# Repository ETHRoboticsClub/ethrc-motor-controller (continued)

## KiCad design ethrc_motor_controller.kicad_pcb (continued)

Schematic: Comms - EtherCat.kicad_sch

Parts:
C115, C118, C120, C122, C123, C124, C125, C126, C127, C128, C129, C130, C131, C132, C133, C134, C135: 100n; C_0402_1005_DensityHigh; Manufacturer Part Number CL05B104KO5NNNC
C116, C117: 10p C0G; C_0402_1005_DensityHigh; Manufacturer Part Number CL05C100JB5NNNC
C119, C121, C161: 1u; C_0603_1608_DensityHigh; Manufacturer Part Number CL10B105KA8NNNC
C136, C137, C138, C139, C140, C141, C142, C143: 10p; C_0402_1005_DensityHigh; Manufacturer Part Number CL05C100JB5NNNC; not fitted
C144, C145: 0.022u; C_0402_1005_DensityHigh; Manufacturer Part Number GCM155R71H223KA55D
C155, C156: 1n X7R 2kV; C_1808_4520Metric; Manufacturer Part Number C1808C102KGRACTU
D18: Red; LED_0603_1608Metric; Manufacturer Part Number LTST-C191KRKT
D19, D24, D25: Green; LED_0603_1608Metric; Manufacturer Part Number LTST-C191KGKT
FB5: 600R@100MHz; L_0603_1608Metric; Manufacturer Part Number BLM18KG601SN1D
J9, J10: SM05B-GHS-TB; JST_GH_SM05B-GHS-TB_1x05-1MP_P1.25mm_Horizontal; Manufacturer Part Number SM05B-GHS-TB
R46, R48, R49, R51, R57, R58, R90, R91: 10k; R_0603_1608_DensityHigh; Manufacturer Part Number CRCW060310K0FKEA
R47, R50, R52, R53: 2.2k; R_0603_1608_DensityHigh; Manufacturer Part Number ERJ-3EKF2201V
R54: 1k; R_0603_1608_DensityHigh; Manufacturer Part Number ERJ-3EKF1001V
R55: 12.1k 1%; R_0603_1608_DensityHigh; Manufacturer Part Number ERJ-3EKF1212V
R56: 22R; R_0402_1005_DensityHigh; Manufacturer Part Number ERJ-2RKF22R0X
R59, R60, R61, R62, R63, R64, R65, R66: 49.9 1%; R_0402_1005_DensityHigh; Manufacturer Part Number ERJ-2RKF49R9X
R67, R68: 330; R_0603_1608_DensityHigh; Manufacturer Part Number ERJ-3EKF3300V
R83, R84: 0R; R_0603_1608_DensityHigh; Manufacturer Part Number CRCW06030000Z0EAHP
R85, R86, R87, R88: 75 1%; R_0603_1608_DensityHigh; Manufacturer Part Number ERJ-3EKF75R0V
T1, T2: H1102NL; Transformer_Pulse_H1100NL; Manufacturer Part Number H1102NL
TP76: ESC_XO_XTAL; TestPoint_Keystone_5000-5004_Miniature; Manufacturer Part Number 5004
TP77: GND; TestPoint_Keystone_5000-5004_Miniature; Manufacturer Part Number 5001
TP78: +3V3_PHY; TestPoint_Pad_D0.5mm
TP79: +1V2_ESC; TestPoint_Pad_D0.5mm
TP80: ESC_OSCVDD12; TestPoint_Pad_D0.5mm
TP81: EE_SCL; TestPoint_Pad_D0.5mm
TP82: EE_SDA; TestPoint_Pad_D0.5mm
TP83: ECAT_P0_TX+; TestPoint_Pad_D0.4mm
TP84: ECAT_P0_TX-; TestPoint_Pad_D0.4mm
TP85: ECAT_P0_RX+; TestPoint_Pad_D0.4mm
TP86: ECAT_P0_RX-; TestPoint_Pad_D0.4mm
TP87: ECAT_P1_TX+; TestPoint_Pad_D0.4mm
TP88: ECAT_P1_TX-; TestPoint_Pad_D0.4mm
TP89: ECAT_P1_RX+; TestPoint_Pad_D0.4mm
TP90: ECAT_P1_RX-; TestPoint_Pad_D0.4mm
U8: 24LC32AT-I/OT; SOT-23-5; Manufacturer Part Number 24LC32AT-I/OT
U9: LAN9253-V/R4X; QFN64_R4X_MCH; Manufacturer Part Number LAN9253-V/R4X
Y1: 25MHz 8pF; ABM8G_ABR; Manufacturer Part Number ABM8G-25.000MHZ-4Y-T3

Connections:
+1V2_ESC: C122.1, C124.1, C126.1, C128.1, C130.1, C161.1, TP79.1, U9.6 (VDDCR), U9.24 (VDDCR), U9.38 (VDDCR), U9.56 (VDD12TX1), U9.59 (VDD12TX2)
+3V3: C115.2, C121.1, C123.1, C125.1, C127.1, C129.1, C131.1, C132.1, D19.2 (A), FB5.2, R49.2, R50.1, R51.1, R52.1, R90.1, R91.1, U8.4 (VCC), U9.5 (VDD33), U9.7 (REG_EN), U9.14 (VDDIO), U9.20 (VDDIO), U9.32 (VDDIO), U9.37 (VDDIO), U9.47 (VDDIO); also elsewhere on the board
+3V3_PHY: C133.1, C134.1, C135.1, C144.1, C145.1, FB5.1, R59.1, R60.1, R61.1, R62.1, R63.1, R64.1, R65.1, R66.1, T1.2 (TCT), T1.7 (RCT), T2.2 (TCT), T2.7 (RCT), TP78.1, U9.51 (VDD33TXRX1), U9.58 (VDD33BIAS), U9.64 (VDD33TXRX2)
/Project Architecture/Comms - EtherCat/ECAT_P0_CBL_RX+: J9.3, T1.11 (RX+)
/Project Architecture/Comms - EtherCat/ECAT_P0_CBL_RX-: J9.2, T1.9 (RX-)
/Project Architecture/Comms - EtherCat/ECAT_P0_CBL_TX+: J9.5, T1.16 (TX+)
/Project Architecture/Comms - EtherCat/ECAT_P0_CBL_TX-: J9.4, T1.14 (TX-)
/Project Architecture/Comms - EtherCat/ECAT_P0_RX+: C140.1, R63.2, T1.1 (TD+), TP85.1, U9.55 (RXPA)
/Project Architecture/Comms - EtherCat/ECAT_P0_RX-: C142.1, R65.2, T1.3 (TD-), TP86.1, U9.54 (RXNA)
/Project Architecture/Comms - EtherCat/ECAT_P0_TX+: C136.1, R59.2, T1.6 (RD+), TP83.1, U9.53 (TXPA)
/Project Architecture/Comms - EtherCat/ECAT_P0_TX-: C138.1, R61.2, T1.8 (RD-), TP84.1, U9.52 (TXNA)
/Project Architecture/Comms - EtherCat/ECAT_P1_CBL_RX+: J10.3, T2.11 (RX+)
/Project Architecture/Comms - EtherCat/ECAT_P1_CBL_RX-: J10.2, T2.9 (RX-)
/Project Architecture/Comms - EtherCat/ECAT_P1_CBL_TX+: J10.5, T2.16 (TX+)
/Project Architecture/Comms - EtherCat/ECAT_P1_CBL_TX-: J10.4, T2.14 (TX-)
/Project Architecture/Comms - EtherCat/ECAT_P1_RX+: C141.1, R64.2, T2.8 (RD-), TP89.1, U9.60 (RXPB)
/Project Architecture/Comms - EtherCat/ECAT_P1_RX-: C143.1, R66.2, T2.6 (RD+), TP90.1, U9.61 (RXNB)
/Project Architecture/Comms - EtherCat/ECAT_P1_TX+: C137.1, R60.2, T2.3 (TD-), TP87.1, U9.62 (TXPB)
/Project Architecture/Comms - EtherCat/ECAT_P1_TX-: C139.1, R62.2, T2.1 (TD+), TP88.1, U9.63 (TXNB)
/Project Architecture/Comms - EtherCat/EE_SCL: R50.2, TP81.1, U8.1 (SCL), U9.43 (EESCL/EE_EMUL2)
/Project Architecture/Comms - EtherCat/EE_SDA: R52.2, TP82.1, U8.3 (SDA), U9.42 (EESDA/EE_EMUL1)
/Project Architecture/Comms - EtherCat/ESC_CLK25: R54.1, U9.8 (CLK_25/XTAL_MODE)
/Project Architecture/Comms - EtherCat/ESC_CS: R90.2, U9.50 (SCS#); also elsewhere on the board
/Project Architecture/Comms - EtherCat/ESC_ERR: R47.1, R48.1, U9.9 (ERRLED/100FD_B)
/Project Architecture/Comms - EtherCat/ESC_IRQ: R91.2, U9.44 (IRQ); also elsewhere on the board
/Project Architecture/Comms - EtherCat/ESC_LINK0: R58.1, R67.1, U9.48 (LINKACTLED0/CHIP_MODE0)
/Project Architecture/Comms - EtherCat/ESC_LINK1: R57.1, R68.1, U9.46 (LINKACTLED1/CHIP_MODE1)
/Project Architecture/Comms - EtherCat/ESC_MISO: R56.2; also elsewhere on the board
/Project Architecture/Comms - EtherCat/ESC_MISO_ESC: R56.1, U9.13 (SO/SIO1)
/Project Architecture/Comms - EtherCat/ESC_MOSI: U9.17 (SI/SIO0); also elsewhere on the board
/Project Architecture/Comms - EtherCat/ESC_OSCVDD12: C119.1, C120.1, TP80.1, U9.3 (OSCVDD12)
/Project Architecture/Comms - EtherCat/ESC_RBIAS: R55.1, U9.57 (RBIAS)
/Project Architecture/Comms - EtherCat/ESC_RST: C118.1, R51.2, U9.11 (RST#); also elsewhere on the board
/Project Architecture/Comms - EtherCat/ESC_RUN: R49.1, R53.2, U9.45 (RUNLED/E2PSIZE)
/Project Architecture/Comms - EtherCat/ESC_SCLK: U9.19 (SCK); also elsewhere on the board
/Project Architecture/Comms - EtherCat/ESC_SYNC0: U9.34 (SYNC0/LATCH0); also elsewhere on the board
/Project Architecture/Comms - EtherCat/ESC_SYNC1: U9.18 (SYNC1/LATCH1); also elsewhere on the board
/Project Architecture/Comms - EtherCat/ESC_XI: R84.1, U9.1 (OSCI)
/Project Architecture/Comms - EtherCat/ESC_XO: R83.2, U9.2 (OSCO)
/Project Architecture/Comms - EtherCat/ESC_XO_XTAL: C116.1, R83.1, TP76.1, Y1.1
CHASSIS: C155.2, C156.2, J9.1, J9.MP1, J9.MP2, J10.1, J10.MP1, J10.MP2; also elsewhere on the board
GND: C115.1, C116.2, C117.2, C118.2, C119.2, C120.2, C121.2, C122.2, C123.2, C124.2, C125.2, C126.2, C127.2, C128.2, C129.2, C130.2, C131.2, C132.2, C133.2, C134.2, C135.2, C136.2, C137.2, C138.2, C139.2, C140.2, C141.2, C142.2, C143.2, C144.2, C145.2, C161.2, D18.1 (K), D24.1 (K), D25.1 (K), R46.1, R48.2, R54.2, R55.2, R57.2, R58.2, TP77.1, U8.2 (VSS), U9.4 (OSCVSS), U9.41 (TESTMODE), U9.65 (VSS(EP)), Y1.2, Y1.4; also elsewhere on the board
unnamed: C117.1, R84.2, Y1.3
unnamed: C155.1, R85.2, R86.2
unnamed: C156.1, R87.2, R88.2
unnamed: D18.2 (A), R47.2
unnamed: D19.1 (K), R53.1
unnamed: D24.2 (A), R67.2
unnamed: D25.2 (A), R68.2
unnamed: R86.1, T1.10 (RXCT)
unnamed: R85.1, T1.15 (TXCT)
unnamed: R88.1, T2.10 (RXCT)
unnamed: R87.1, T2.15 (TXCT)
unnamed: R46.2, U8.5 (WP)

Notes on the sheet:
strap CHIP_MODE0
25 MHz crystal
+3V3_PHY: pins 51, 58, 64, T1/T2 centre taps, FB5 output
22R at U9
SII EEPROM (I2C address 0x50)
tie low
strap 100FD_B
Mode strap, reset, SPI MISO series
crystal mode
+1V2_ESC (internal regulator): C161 1u low-ESR (DS00003421B 4.1.1) at VDDCR pin 6; 24, 38, 56, 59 100n each
ETHERCAT - LAN9253 (SPI PDI, 2 PORTS), Magnetics, SII EEPROM
49.9R terminations to +3V3_PHY (at the LAN9253 pins)
EtherCAT indicators + strap resistors (straps read at reset)
unused in SPI mode
H1102NL magnetics, Bob Smith (75R + 1n 2kV), JST-GH connectors
+3V3: VDD33 (5) 1u+100n, VDDIO (14, 20, 32, 37, 47) 100n each, U3 100n
strap CHIP_MODE1
strap E2PSIZE=1
EtherCAT test points (TP76/TP77 hooks on the BOM, the others are bare pads)
LAYOUT NOTE: ETHERCAT * TX/RX pairs 100 ohm differential, matched in-pair, short; 49.9R at the U9 pins. * Keep PHY side and cable side of T1/T2 apart; no GND plane under the cable side and the GH connectors except the Bob Smith cap return; C155/C156 right at the centre taps, returned to CHASSIS. * 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
DESIGN NOTE: WP low: master can write the SII
[${#}] ${TITLE}
DESIGN NOTE: T1/T2 chip side deliberately swapped (2026-11-22) so every pair routes on L1 without vias: port 0: U9 TX pair -> T1 RD pins 6/8, RX pair -> TD pins 1/3 (Auto-MDIX sorts TX/RX); port 1: P and N exchanged in both pairs at T2 (automatic polarity correction). Microchip LAN9253 HW design ch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

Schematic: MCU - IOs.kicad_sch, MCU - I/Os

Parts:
C12, C13: 100n X7R 50V; C_0402_1005_DensityHigh; Manufacturer Part Number GCM155R71H104KE02J
C14, C15, C16: 1n; C_0402_1005_DensityHigh; Manufacturer Part Number AC0402KRX7R8BB102
D1: PESD4USB3U-TBSX; SOT1176D; Manufacturer Part Number PESD4USB3U-TBSX
J15: Conn_ARM_SWD_TagConnect_TC2030-NL; Tag-Connect_TC2030-IDC-NL_2x03_P1.27mm_Vertical
R1, R2, R3, R4, R5, R6, R7: 22R 1%; R_0402_1005_DensityHigh; Manufacturer Part Number ERJ-2RKF22R0X
R8, R9: 22; R_0402_1005_DensityHigh; Manufacturer Part Number RC0402FR-0722RL
R77: 10k; R_0402_1005_DensityHigh; Manufacturer Part Number CRCW040210K0FKED
TP1: MOTOR_ENABLE; TestPoint_Pad_D0.5mm
TP2: MOTOR_HIZ; TestPoint_Pad_D0.5mm
TP3: MOTOR_FAULT; TestPoint_Pad_D0.5mm
TP4: DRV_SCLK; TestPoint_Pad_D0.5mm
TP5: DRV_MISO; TestPoint_Pad_D0.5mm
TP6: DRV_MOSI; TestPoint_Pad_D0.5mm
TP7: DRV_CS; TestPoint_Pad_D0.5mm
TP8: PWM_PHASEA; TestPoint_Pad_D0.5mm
TP9: PWM_PHASEB; TestPoint_Pad_D0.5mm
TP10: PWM_PHASEC; TestPoint_Pad_D0.5mm
TP11: SOA; TestPoint_Pad_D0.5mm
TP12: SOB; TestPoint_Pad_D0.5mm
TP13: SOC; TestPoint_Pad_D0.5mm
TP14: SWDIO; TestPoint_Pad_D0.5mm
TP15: SWCLK; TestPoint_Pad_D0.5mm
TP16: NRST; TestPoint_Pad_D0.5mm
TP17: ESC_RST; TestPoint_Pad_D0.5mm
TP18: ESC_SCLK; TestPoint_Pad_D0.5mm
TP19: ESC_MISO; TestPoint_Pad_D0.5mm
TP20: ESC_MOSI; TestPoint_Pad_D0.5mm
TP21: ESC_CS; TestPoint_Pad_D0.5mm
TP22: ESC_IRQ; TestPoint_Pad_D0.5mm
TP23: ESC_SYNC0; TestPoint_Pad_D0.5mm
TP24: ENC_SCLK; TestPoint_Pad_D0.5mm
TP25: ENC_MISO; TestPoint_Pad_D0.5mm
TP26: ENC_MOSI; TestPoint_Pad_D0.5mm
TP27: ENC_BRD_CS; TestPoint_Pad_D0.5mm
TP28: ENC_EXT_CS; TestPoint_Pad_D0.5mm
TP31: LED_DBG; TestPoint_Pad_D0.5mm
TP32: LED_PWR; TestPoint_Pad_D0.5mm
TP33: FD_CAN_RX; TestPoint_Pad_D0.5mm
TP34: FDCAN_TX; TestPoint_Pad_D0.5mm
TP35: FAN_CTRL; TestPoint_Pad_D0.5mm
TP36: SENSE_TEMP_MOT; TestPoint_Pad_D0.5mm
TP37: SENSE_TEMP_FET; TestPoint_Pad_D0.5mm
TP38: SENSE_VBAT; TestPoint_Pad_D0.5mm
TP75: ESC_SYNC1; TestPoint_Pad_D0.5mm
U1: STM32G474RET3; LQFP-64_10x10mm_P0.5mm; Manufacturer Part Number STM32G474RET3

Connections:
+3V3: C12.1, J15.5 (GND); also elsewhere on the board
/Project Architecture/Comms - EtherCat/ESC_CS: TP21.1, U1.33 (PB11); also elsewhere on the board
/Project Architecture/Comms - EtherCat/ESC_IRQ: TP22.1, U1.41 (PC9); also elsewhere on the board
/Project Architecture/Comms - EtherCat/ESC_MISO: TP19.1, U1.36 (PB14); also elsewhere on the board
/Project Architecture/Comms - EtherCat/ESC_MOSI: R3.2, TP20.1; also elsewhere on the board
/Project Architecture/Comms - EtherCat/ESC_RST: TP17.1, U1.44 (PA10); also elsewhere on the board
/Project Architecture/Comms - EtherCat/ESC_SCLK: R4.2, TP18.1; also elsewhere on the board
/Project Architecture/Comms - EtherCat/ESC_SYNC0: TP23.1, U1.39 (PC7); also elsewhere on the board
/Project Architecture/Comms - EtherCat/ESC_SYNC1: TP75.1, U1.40 (PC8); also elsewhere on the board
/Project Architecture/Comms - FD-CAN/FDCAN_RX: TP33.1, U1.58 (PB5); also elsewhere on the board
/Project Architecture/Comms - FD-CAN/FDCAN_TX: TP34.1, U1.59 (PB6); also elsewhere on the board
/Project Architecture/MCU - IOs/BOARD_VERSION: U1.18 (PA4); also elsewhere on the board
/Project Architecture/MCU - IOs/BOOT0: R77.1, U1.61 (PB8)
/Project Architecture/MCU - IOs/DRV_CS: TP7.1, U1.56 (PB3); also elsewhere on the board
/Project Architecture/MCU - IOs/DRV_MISO: TP5.1, U1.53 (PC11); also elsewhere on the board
/Project Architecture/MCU - IOs/DRV_MOSI: R2.1, TP6.1; also elsewhere on the board
/Project Architecture/MCU - IOs/DRV_MOSI_MCU: R2.2, U1.54 (PC12)
/Project Architecture/MCU - IOs/DRV_SCLK: R1.1, TP4.1; also elsewhere on the board
/Project Architecture/MCU - IOs/DRV_SCLK_MCU: R1.2, U1.52 (PC10)
/Project Architecture/MCU - IOs/ENC_BRD_CS: TP27.1, U1.26 (PB2); also elsewhere on the board
/Project Architecture/MCU - IOs/ENC_EXT_CS: TP28.1, U1.51 (PA15); also elsewhere on the board
/Project Architecture/MCU - IOs/ENC_MISO: TP25.1, U1.57 (PB4); also elsewhere on the board
/Project Architecture/MCU - IOs/ENC_MOSI: R9.2, TP26.1; also elsewhere on the board
/Project Architecture/MCU - IOs/ENC_MOSI_MCU: R9.1, U1.21 (PA7)
/Project Architecture/MCU - IOs/ENC_SCLK: R8.2, TP24.1; also elsewhere on the board
/Project Architecture/MCU - IOs/ENC_SCLK_MCU: R8.1, U1.19 (PA5)
/Project Architecture/MCU - IOs/ESC_MOSI_MCU: R3.1, U1.37 (PB15)
/Project Architecture/MCU - IOs/ESC_SCLK_MCU: R4.1, U1.35 (PB13)
/Project Architecture/MCU - IOs/FAN_CTRL: TP35.1, U1.55 (PD2)
/Project Architecture/MCU - IOs/FILTER_SOA: C14.1, R5.1, U1.17 (PA3)
/Project Architecture/MCU - IOs/FILTER_SOB: C15.1, R6.1, U1.20 (PA6)
/Project Architecture/MCU - IOs/FILTER_SOC: C16.1, R7.1, U1.25 (PB1)
/Project Architecture/MCU - IOs/LED_DBG: TP31.1, U1.30 (PB10); also elsewhere on the board
/Project Architecture/MCU - IOs/LED_FAULT: TP32.1, U1.38 (PC6); also elsewhere on the board
/Project Architecture/MCU - IOs/MOTOR_ENABLE: TP1.1, U1.3 (PC14); also elsewhere on the board
/Project Architecture/MCU - IOs/MOTOR_FAULT: TP3.1, U1.8 (PC0); also elsewhere on the board
/Project Architecture/MCU - IOs/MOTOR_HIZ: TP2.1, U1.4 (PC15); also elsewhere on the board
/Project Architecture/MCU - IOs/NRST: C13.1, D1.1 (K), D1.10 (K), J15.3 (~RESET), TP16.1, U1.7 (PG10)
/Project Architecture/MCU - IOs/PWM_PHASEA: TP8.1, U1.14 (PA2); also elsewhere on the board
/Project Architecture/MCU - IOs/PWM_PHASEB: TP9.1, U1.13 (PA1); also elsewhere on the board
/Project Architecture/MCU - IOs/PWM_PHASEC: TP10.1, U1.12 (PA0); also elsewhere on the board
/Project Architecture/MCU - IOs/SENSE_TEMP_FET: TP37.1, U1.34 (PB12); also elsewhere on the board
/Project Architecture/MCU - IOs/SENSE_TEMP_MOT: TP36.1, U1.42 (PA8); also elsewhere on the board
/Project Architecture/MCU - IOs/SENSE_VBAT: TP38.1, U1.43 (PA9); also elsewhere on the board
/Project Architecture/MCU - IOs/SOA: R5.2, TP11.1; also elsewhere on the board
/Project Architecture/MCU - IOs/SOB: R6.2, TP12.1; also elsewhere on the board
/Project Architecture/MCU - IOs/SOC: R7.2, TP13.1; also elsewhere on the board
/Project Architecture/MCU - IOs/SWCLK: D1.4 (K), D1.7 (K), J15.4 (SWCLK), TP15.1, U1.50 (PA14)
/Project Architecture/MCU - IOs/SWDIO: D1.5 (K), D1.6 (K), J15.2 (SWDIO), TP14.1, U1.49 (PA13)
GND: C12.2, C13.2, C14.2, C15.2, C16.2, D1.3 (A), D1.8 (A), J15.1 (VCC), R77.2; also elsewhere on the board

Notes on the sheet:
Flexible I/O worked examples
open-drain output
References:
Flexible I/O source configuration
DESIGN NOTE: Ideally TVS should be connected to chassis but makes it harder to route.
EtherCAT Slave Controller
FD-CAN
LEDs
SWD (Debug) Port
Gate Driver
Fan
Sense
Position Sense
LAYOUT NOTE: Shunt amplifier output low-pass filters. Place near MCU ADC pins.
Board Version Selection
[${#}] ${TITLE}
User LEDs
5Mbps FD-CAN Bus
DESIGN NOTE: Do not forget to flash option bytes when flashing for the first time.
Low-Side Fan Control
Debug
LAYOUT NOTE: Footprint deviates from datasheet and IPC7351 to allow for soldermask sliver between pads according to PCBWay design rules.
Microcontroller I/O Domain
Temperature Sense
Battery Voltage Sense
Test Points
DESIGN NOTE: We use the LQFP64 version to have extra pins for controlling an external fan.
DESIGN NOTE: Only connect GND if connected device does not share ground!
Connections to Gate Driver
Connection to EtherCat Subdevice Controller

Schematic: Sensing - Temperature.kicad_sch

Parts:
C110, C111: 100n X7R 50V; C_0402_1005_DensityHigh; Manufacturer Part Number GCM155R71H104KE02J
D15, D16: BAT41KFILM; D_SOD-523; Manufacturer Part Number BAT41KFILM
J7: S2B-PH-SM4-TB; JST_B2B-PH-SM4-TB; Manufacturer Part Number S2B-PH-SM4-TB
R41, R42: 10k 1%; R_0402_1005_DensityHigh; Manufacturer Part Number RT0402FRE0710KL
TH1: 47k 1% NTC; R_0402_1005_DensityHigh; Manufacturer Part Number NCP15WB473F03RC

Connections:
+A3V3: D15.1 (K), D16.1 (K), R41.1, R42.1; also elsewhere on the board
/Project Architecture/MCU - IOs/SENSE_TEMP_FET: C110.1, D15.2 (A), R41.2, TH1.1; also elsewhere on the board
/Project Architecture/MCU - IOs/SENSE_TEMP_MOT: C111.1, D16.2 (A), J7.1, R42.2; also elsewhere on the board
CHASSIS: J7.MP1, J7.MP2; also elsewhere on the board
GND: C110.2, C111.2, J7.2, TH1.2; also elsewhere on the board

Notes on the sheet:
LAYOUT NOTE: NTCs must be placed close and thermally coupled to relevant heat source. Route away from noisy traces.
MOSFETs Temperature Sensing
Motor Temperature Sensing
[${#}] ${TITLE}
DESIGN NOTE: Ideally connect thermistor with nominal B-Constant 4050-4099K
DESIGN NOTE: Diodes protect against over-voltage.
DESIGN NOTE: Nominal B-Constant 4050-4099K
DESIGN NOTE: Resistor chosen for a 10k 3950K motor thermistor. See make_thermistor_table.py in the firmware repository for more details.

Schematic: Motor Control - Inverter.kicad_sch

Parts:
C98, C99, C102, C103, C106, C107: 3n3 X7R 100V; C_0402_1005_DensityHigh; Manufacturer Part Number GRM155R72A332KA01D; not fitted
C100, C104, C108: 100n X7R 100V; C_1206_3216_DensityHighest; Manufacturer Part Number C1206C104K1RACAUTO
C101, C105, C109: 4u7 X7R 100V; C_1206_3216_DensityHighest; Manufacturer Part Number GRJ31CZ72A475KE01L
D4, D5, D6, D7, D8, D9, D10, D11, D12: BAT41KFILM; D_SOD-523; Manufacturer Part Number BAT41KFILM
J4: Phase A; Pad_Square_Vias_6.5x6.5mm
J5: Phase B; Pad_Square_Vias_6.5x6.5mm
J6: Phase C; Pad_Square_Vias_6.5x6.5mm
NT3: SHNTA_P; NetTie-2_SMD_Pad0.2mm
NT4: SRC_HS_A; NetTie-2_SMD_Pad0.4mm
NT5: SHNTA_N; NetTie-2_SMD_Pad0.2mm
NT6: SHNTB_P; NetTie-2_SMD_Pad0.2mm
NT7: SHNTB_N; NetTie-2_SMD_Pad0.2mm
NT8: SRC_HS_B; NetTie-2_SMD_Pad0.3mm
NT9: SHNTC_P; NetTie-2_SMD_Pad0.2mm
NT10: SHNTC_N; NetTie-2_SMD_Pad0.2mm
NT11: SRC_HS_C; NetTie-2_SMD_Pad0.4mm
Q1, Q2, Q3, Q4, Q5, Q11: FDMT80080DC; FDMT80040DC; Manufacturer Part Number FDMT80080DC; Mouser Part Number 512-FDMT80080DC
R18, R19, R23, R24, R28, R29: 7R5 1% 1/2W; R_0805_2012_DensityHigh; Manufacturer Part Number CRCW08057R50FKEAHP
R20, R25, R30: 0m5 1% 2W; HCS1206FTL500; Manufacturer Part Number HCS1206FTL500
R21, R22, R26, R27, R31, R32: 5R 1% 0.4W; R_0805_2012_DensityHigh; Manufacturer Part Number CSRT0603FT5R00; not fitted

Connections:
+VBAT: C100.1, C101.1, C104.1, C105.1, C108.1, C109.1, Q2.5, Q2.6, Q2.7, Q2.8, Q4.5, Q4.6, Q4.7, Q4.8, Q11.5, Q11.6, Q11.7, Q11.8, R21.2, R26.2, R31.2; also elsewhere on the board
/Project Architecture/Motor Control - Top Level/GHA: D4.1 (K), R18.2; also elsewhere on the board
/Project Architecture/Motor Control - Top Level/GHB: D9.1 (K), R24.1; also elsewhere on the board
/Project Architecture/Motor Control - Top Level/GHC: D11.1 (K), R29.1; also elsewhere on the board
/Project Architecture/Motor Control - Top Level/GLA: D5.1 (K), R19.1; also elsewhere on the board
/Project Architecture/Motor Control - Top Level/GLB: D7.1 (K), R23.1; also elsewhere on the board
/Project Architecture/Motor Control - Top Level/GLC: D10.1 (K), R28.1; also elsewhere on the board
/Project Architecture/Motor Control - Top Level/Motor Control - Inverter/FET_GHA: D4.2 (A), Q11.1, R18.1
/Project Architecture/Motor Control - Top Level/Motor Control - Inverter/FET_GHB: D9.2 (A), Q2.1, R24.2
/Project Architecture/Motor Control - Top Level/Motor Control - Inverter/FET_GHC: D11.2 (A), Q4.1, R29.2
/Project Architecture/Motor Control - Top Level/Motor Control - Inverter/FET_GLA: D5.2 (A), D6.1 (K), Q1.1, R19.2
/Project Architecture/Motor Control - Top Level/Motor Control - Inverter/FET_GLB: D7.2 (A), D8.1 (K), Q3.1, R23.2
/Project Architecture/Motor Control - Top Level/Motor Control - Inverter/FET_GLC: D10.2 (A), D12.1 (K), Q5.1, R28.2
/Project Architecture/Motor Control - Top Level/Motor Control - Inverter/PHA: C98.1, C99.2, J4.1, NT4.2, Q1.5, Q1.6, Q1.7, Q1.8, Q11.2, Q11.3, Q11.4
/Project Architecture/Motor Control - Top Level/Motor Control - Inverter/PHB: C102.1, C103.2, J5.1, NT8.2, Q2.2, Q2.3, Q2.4, Q3.5, Q3.6, Q3.7, Q3.8
/Project Architecture/Motor Control - Top Level/Motor Control - Inverter/PHC: C106.1, C107.2, J6.1, NT11.2, Q4.2, Q4.3, Q4.4, Q5.5, Q5.6, Q5.7, Q5.8
/Project Architecture/Motor Control - Top Level/Motor Control - Inverter/SNUBH_A: C98.2, R21.1
/Project Architecture/Motor Control - Top Level/Motor Control - Inverter/SNUBH_B: C102.2, R26.1
/Project Architecture/Motor Control - Top Level/Motor Control - Inverter/SNUBH_C: C106.2, R31.1
/Project Architecture/Motor Control - Top Level/Motor Control - Inverter/SNUBL_A: C99.1, R22.2
/Project Architecture/Motor Control - Top Level/Motor Control - Inverter/SNUBL_B: C103.1, R27.2
/Project Architecture/Motor Control - Top Level/Motor Control - Inverter/SNUBL_C: C107.1, R32.2
/Project Architecture/Motor Control - Top Level/Motor Control - Inverter/SRC_LS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: C100.2, NT3.1, Q1.2, Q1.3, Q1.4, R20.2, R22.1
/Project Architecture/Motor Control - Top Level/Motor Control - Inverter/SRC_LS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: C104.2, NT6.2, Q3.2, Q3.3, Q3.4, R25.2, R27.1
/Project Architecture/Motor Control - Top Level/Motor Control - Inverter/SRC_LS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: C108.2, NT9.2, Q5.2, Q5.3, Q5.4, R30.2, R32.1
/Project Architecture/Motor Control - Top Level/SA+: NT3.2; also elsewhere on the board
/Project Architecture/Motor Control - Top Level/SA-: NT5.1; also elsewhere on the board
/Project Architecture/Motor Control - Top Level/SB+: NT6.1; also elsewhere on the board
/Project Architecture/Motor Control - Top Level/SB-: NT7.1; also elsewhere on the board
/Project Architecture/Motor Control - Top Level/SC+: NT9.1; also elsewhere on the board
/Project Architecture/Motor Control - Top Level/SC-: NT10.1; also elsewhere on the board
/Project Architecture/Motor Control - Top Level/SHA: NT4.1; also elsewhere on the board
/Project Architecture/Motor Control - Top Level/SHB: NT8.1; also elsewhere on the board
/Project Architecture/Motor Control - Top Level/SHC: NT11.1; also elsewhere on the board
GND: C101.2, C105.2, C109.2, D6.2 (A), D8.2 (A), D12.2 (A), NT5.2, NT7.2, NT10.2, R20.1, R25.1, R30.1; also elsewhere on the board

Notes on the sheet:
Best Practices for Board Layout of Motor Drivers
Proper RC Snubber Design for Motor Drivers
System Design Considerations for High-Power Motor Driver Applications
DESIGN NOTE: A gate drive current that is too large can damage the FETs!
[${#}] ${TITLE}
LAYOUT NOTE: High current traces must be carefully designed. Ensure ground return path does not cross sensitive parts of the board. Use multiple planes for higher current carrying capacity.
LAYOUT NOTE: Keep sufficient clearance between power nets according to IPC-2221/IEC60664-1.
DESIGN NOTE: Replace with zeners?
DESIGN NOTE: Low-side Schottky diodes protect the FET's gate against negative transients.
DESIGN NOTE: Gate resistor + discharge diode
DESIGN NOTE: Local bulk capacitors.
DESIGN NOTE: Optional RC snubber to reduce ringing.

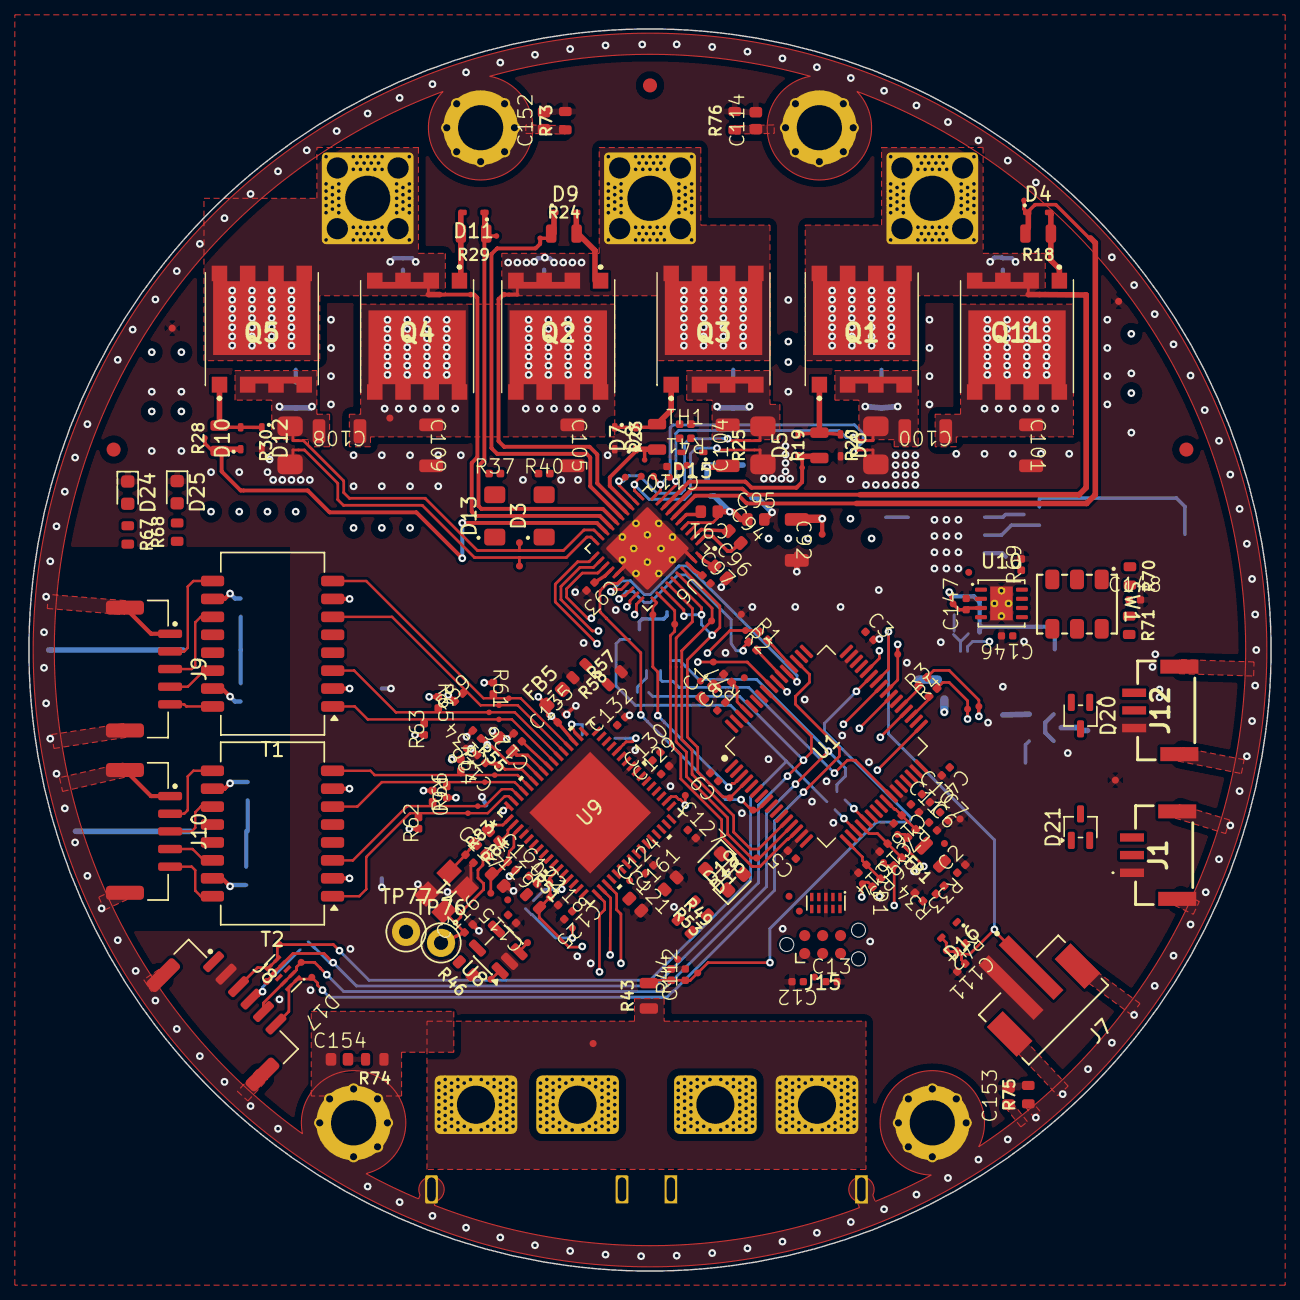
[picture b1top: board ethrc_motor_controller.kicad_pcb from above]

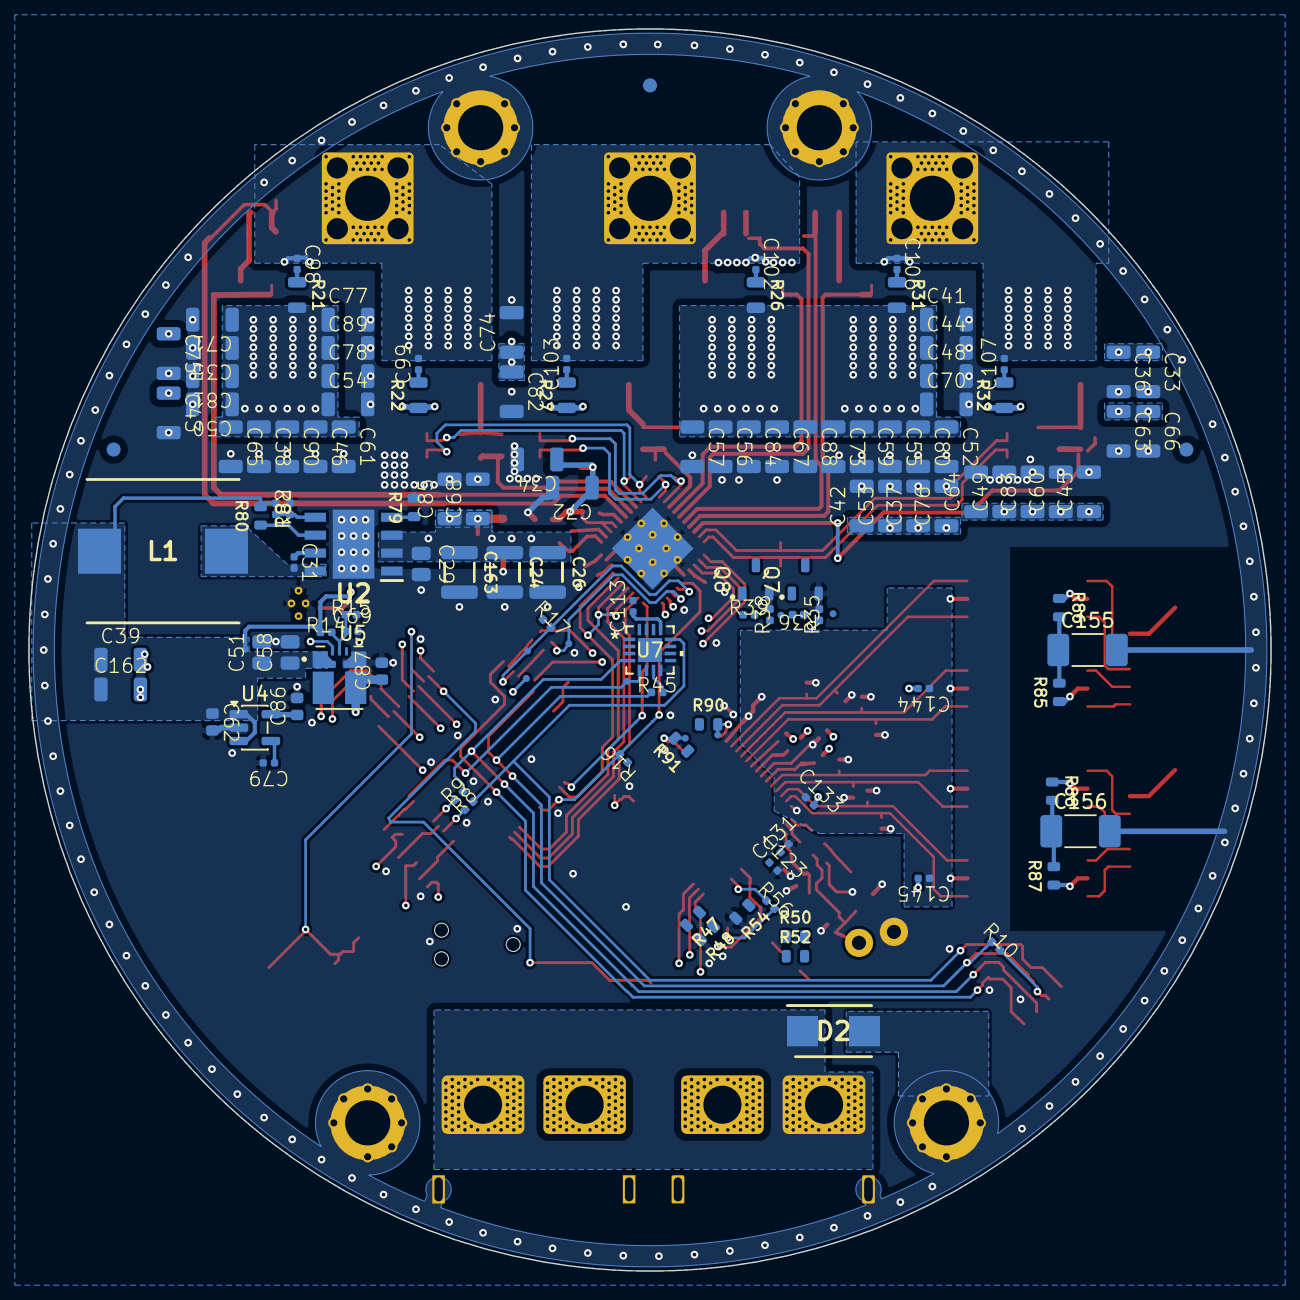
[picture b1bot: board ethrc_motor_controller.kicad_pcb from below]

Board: 6 copper layers, 88.0 x 88.0 mm, 380 parts (130 on the bottom side), 157 nets.

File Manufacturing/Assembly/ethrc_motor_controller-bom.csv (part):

Row,Quantity Per PCB,References,Value,Datasheet,Footprint,Description,Manufacturer,Manufacturer Part Number,Supplier 1,Supplier Part Number 1
1,2,C116 C117,10p C0G,https://mm.digikey.com/Volume0/opasdata/d220001/medias/docus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,C_0402_1005_DensityHigh,Unpolarized capacitor,Samsung Electro-Mechanics,CL05C100JB5NNNC,Mouser,187-CL05C100JB5NNNC
2,3,C14 C15 C16,1n,https://www.yageo.com/upload/media/product/app/datasheet/mlc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,C_0402_1005_DensityHigh,"Unpolarized capacitor, small symbol",YAGEO,AC0402KRX7R8BB102,Digikey,311-3065-1-ND
3,1,C148,4n7 X7R 100V,https://www.murata.com/-/media/webrenewal/support/library/ca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,C_0402_1005_DensityHigh,"Unpolarized capacitor, small symbol",Murata Electronics,GCM155R72A472KA37D,Digikey,490-4765-1-ND
4,1,C69,10n,https://www.mouser.com/datasheet/3/76/1/GRM155R71C103KA01-01A.pdf,C_0402_1005_DensityHigh,"10nF 16V, X7R, ±10%, 0402, MLCC",Murata Electronics,GRM155R71C103KA01D,Mouser,81-GRM36X103K16
5,1,C79,10n,https://mm.digikey.com/Volume0/opasdata/d220001/medias/docus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,C_0402_1005_DensityHigh,"10nF 100V, X7R, ±10%, 0402, MLCC",Taiyo Yuden,HMR105B7103KV-F,Digikey,587-HMR105B7103KV-FCT-ND
6,2,C144 C145,0.022u,https://pim.murata.com/asset/pim4/ceramicCapacitorSMD/GCM155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,C_0402_1005_DensityHigh,Unpolarized capacitor,Murata Electronics,GCM155R71H223KA55D,Mouser,81-GCM155R71H223KA5D
7,1,C94,47n X7R 100V,https://connect.kemet.com:7667/gateway/IntelliData-Component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,C_0603_1608_DensityHigh,"Unpolarized capacitor, small symbol",KEMET,C0603C473K1RECAUTO,Digikey,399-14764-1-ND
8,13,C3 C4 C5 C8 C10 C11 C12 C13 C110 C111 C112 C146 C147,100n X7R 50V,https://search.murata.co.jp/Ceramy/image/img/A01X/G101/ENG/G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,C_0402_1005_DensityHigh,"Unpolarized capacitor, small symbol",Murata Electronics,GCM155R71H104KE02J,Digikey,490-14514-1-ND
9,3,C100 C104 C108,100n X7R 100V,https://connect.kemet.com:7667/gateway/IntelliData-Component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,C_1206_3216_DensityHighest,"Unpolarized capacitor, small symbol",KEMET,C1206C104K1RACAUTO,Digikey,399-7008-1-ND
10,17,C115 C118 C120 C122 C123 C124 C125 C126 C127 C128 C129 C130 C131 C132 C133 C134 C135,100n,https://mm.digikey.com/Volume0/opasdata/d220001/medias/docus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,C_0402_1005_DensityHigh,Unpolarized capacitor,Samsung Electro-Mechanics,CL05B104KO5NNNC,Mouser,187-CL05B104KO5NNNC
11,1,C29,100n,https://product.tdk.com/system/files/dam/doc/product/capacit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,C_0805_2012_DensityHigh,"100nF 100V, X7R, ±10%, 0805, MLCC",TDK Corporation,C2012X7R2A104K125AA,Mouser,810-C2012X7R2A104K
12,1,C31,100n,https://www.mouser.com/datasheet/3/76/2/GRM155R71C104KA88_01A.pdf,C_0402_1005_DensityHigh,"100nF 16V, X7R, ±10%, 0402, MLCC",Murata Electronics,GRM155R71C104KA88D,Mouser,81-GRM155R71C104KA88
13,1,C58,100n,https://www.mouser.com/datasheet/3/5926/1/KGM_X7R.pdf,C_0805_2012_DensityHigh,"100nF 25V, X7R, ±10%, 0805, MLCC",KYOCERA AVX,08053C104KAT2A,Mouser,581-08053C104K
14,1,C93,100n X7R 16V,https://search.murata.co.jp/Ceramy/image/img/A01X/G101/ENG/G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,C_0402_1005_DensityHigh,"Unpolarized capacitor, small symbol",Murata Electronics,GCM155R71C104KA55D,Digikey,490-4759-1-ND
15,1,C95,100n X7R 100V,https://mm.digikey.com/Volume0/opasdata/d220001/medias/docus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,C_0603_1608_DensityHigh,"Unpolarized capacitor, small symbol",Taiyo Yuden,HMK107B7104KAHT,Digikey,587-6009-1-ND
16,4,C2 C6 C9 C113,1u X7R 10V,https://search.murata.co.jp/Ceramy/image/img/A01X/G101/ENG/G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,C_0402_1005_DensityHigh,"Unpolarized capacitor 1uF 10V, X7R, ±10%, 0402, MLCC",Murata Electronics,GRM155Z71A105KE01J,Digikey,490-GRM155Z71A105KE01JCT-ND
17,3,C119 C121 C161,1u,https://mm.digikey.com/Volume0/opasdata/d220001/medias/docus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,C_0603_1608_DensityHigh,Unpolarized capacitor,Samsung Electro-Mechanics,CL10B105KA8NNNC,Mouser,187-CL10B105KA8NNNC
18,3,C24 C26 C163,1u,https://www.mouser.com/catalog/specsheets/Tayio_Yuden_110202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,C_1210_3225_DensityHigh,"1uF 100V, X7R, ±10%, 1210, MLCC",Taiyo Yuden,MSASH32NSB7105KTNA01,LCSC,C5383033
19,3,C62 C91 C96,1u,https://mm.digikey.com/Volume0/opasdata/d220001/medias/docus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,C_0603_1608_DensityHigh,"1uF 25V, X7R, ±10%, 0603, MLCC Unpolarized capacitor",Taiyo Yuden,TMK107AB7105KAHT,Digikey,587-3467-1-ND
20,1,C97,1u X7R 6.3V,https://search.murata.co.jp/Ceramy/image/img/A01X/G101/ENG/G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,C_0402_1005_DensityHigh,Unpolarized capacitor,Murata Electronics,GRT155R70J105KE01D,Digikey,490-18216-1-ND
21,2,C1 C86,4u7 X7R 16V,https://search.murata.co.jp/Ceramy/image/img/A01X/G101/ENG/G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,C_0603_1608_DensityHigh,"Unpolarized capacitor 4.7uF 16V, X7R, ±10%, 0603, MLCC",Murata Electronics,GRM188Z71C475KE21J,Digikey,490-GRM188Z71C475KE21JCT-ND
22,52,C33 C34 C35 C36 C37 C38 C41 C42 C43 C44 C45 C46 C48 C49 C50 C52 C53 C54 C55 C56 C57 C59 C60 C61 C63 C64 C65 C66 C67 C68 C70 C71 C72 C73 C74 C75 C76 C77 C78 C80 C81 C82 C83 C84 C85 C88 C89 C90 C92 C101 C105 C109,4u7,https://search.murata.co.jp/Ceramy/image/img/A01X/G101/ENG/G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,C_1206_3216_DensityHigh,"4.7uF 100V, X7R, ±10%, 1206, MLCC, soft termination Unpolarized capacitor",Murata Electronics,GRJ31CZ72A475KE01L,Digikey,490-GRJ31CZ72A475KE01LCT-ND
23,1,C7,4u7 X5R 25V,https://www.mouser.ch/datasheet/2/40/CM_Series_e-2835982.pdf,C_0402_1005_DensityHigh,Unpolarized capacitor,KYOCERA AVX,CM05X5R475M25AH,Mouser,581-CM05X5R475M25AH
24,1,C51,10u,https://www.mouser.com/datasheet/3/508/1/KEM_C1006_X5R_SMD.pdf,C_0805_2012_DensityHigh,"10uF 10V, X5R, ±10%, 0805, MLCC",KEMET,C0805C106K8PACTU,Mouser,80-C0805C106K8P
25,1,C87,22u,https://www.mouser.com/datasheet/3/76/2/GRM188R60J226MEA0_01A.pdf,C_0603_1608_DensityHigh,"22uF 6.3V, X5R, ±20%, 0603, MLCC",Murata Electronics,GRM188R60J226MEA0D,Mouser,81-GRM188R60J226ME0D
26,2,C39 C162,47u,https://www.mouser.com/datasheet/3/76/2/GRM31CR61A476KE15_04A.pdf,C_1206_3216_DensityHigh,"47uF 10V, X5R, ±10%, 1206, MLCC",Murata Electronics,GRM31CR61A476KE15L,Mouser,81-GRM31CR61A476KE5L
27,4,C114 C152 C153 C154,1n X7R 1kV,https://connect.kemet.com:7667/gateway/IntelliData-Component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,C_0603_1608_DensityHigh,"Unpolarized capacitor, small symbol",KEMET,C0603V102KDRAC7867,Digikey,399-12306-1-ND
28,2,C155 C156,1n X7R 2kV,https://yageogroup.com/content/datasheet/asset/file/KEM_C101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,C_1808_4520Metric,Unpolarized capacitor,KEMET,C1808C102KGRACTU,Digikey,399-C1808C102KGRACTUCT-ND
29,11,D4 D5 D6 D7 D8 D9 D10 D11 D12 D15 D16,BAT41KFILM,https://www.mouser.ch/datasheet/2/389/bat41-1848934.pdf,D_SOD-523,"100V 1A Schottky Diode, SOD-523-2",STMicroelectronics,BAT41KFILM,Digikey,497-5556-1-ND
30,3,D19 D24 D25,Green,https://www.mouser.com/datasheet/3/281/1/LTST_C191KGKT.pdf,LED_0603_1608Metric,"LED green 0603. Pin 1 = cathode, pin 2 = anode.",Lite-On,LTST-C191KGKT,Mouser,859-LTST-C191KGKT
31,2,D20 D21,PESD2CANFD24V-UX,https://assets.nexperia.com/documents/data-sheet/PESD2CANFD2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,SOT-323_SC-70,ESD Suppressors / TVS Diodes PESD2CANFD24V-UX,Nexperia USA Inc.,PESD2CANFD24V-UX,Digikey,1727-PESD2CANFD24V-UXCT-ND
32,1,D1,PESD4USB3U-TBSX,https://assets.nexperia.com/documents/data-sheet/PESD4USB3U-TBS.pdf,SOT1176D,"3.5V (Typ) Clamp 7A (8/20µs) Ipp Tvs Diode Surface Mount, Wettable Flank DFN2510D-10",Nexperia USA Inc.,PESD4USB3U-TBSX,Digikey,1727-PESD4USB3U-TBSXCT-ND
33,1,D17,PESD4USB5B-TBSX,https://assets.nexperia.com/documents/data-sheet/PESD4USB5B-TBS.pdf,SOT1176D,"5.5V (Typ) Clamp 7A (8/20µs) Ipp Tvs Diode Surface Mount, Wettable Flank DFN2510D-10",Nexperia USA Inc.,PESD4USB5B-TBSX,Digikey,1727-PESD4USB5B-TBSXCT-ND
34,1,D18,Red,https://www.mouser.com/datasheet/3/281/1/LTST_C191KRKT.pdf,LED_0603_1608Metric,"LED red 0603. Pin 1 = cathode, pin 2 = anode.",Lite-On,LTST-C191KRKT,Mouser,859-LTST-C191KRKT
35,1,D3,Red,https://www.bivar.com/parts_content/Datasheets/SM1206NHC-IL.pdf,LED_SM1206,"LED red 1206. Pin 1 = cathode, pin 2 = anode.",Bivar Inc.,SM1206NHC-IL,Mouser,749-SM1206NHC-IL
36,1,D2,SMBJ60A,https://m.littelfuse.com/~/media/electronics/datasheets/tvs_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,DIOM5436X244N,"Littelfuse SMBJ60A, Uni-Directional TVS Diode, 600W, 2-Pin DO-214AA",Littelfuse,SMBJ60A,Mouser,576-SMBJ60A
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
